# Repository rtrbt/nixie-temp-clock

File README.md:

# nixie-temp-clock
A modular nixie clock and thermometer based on [Exixe](https://github.com/dekuNukem/exixe).

## Features
- Shows temperature (in °C) and GPS-synchronized time
- Completely modular: the PCB only connects all modules via pin headers

## Hardware
To build your own you need:
- The PCB
- Ten Exixe modules
- One IN-19A, one IN-19V and eight IN-14 tubes
- A high-voltage power supply, as the nixies need 180V to glow. Has to be pin-compatible to [this one](https://www.ebay.com/itm/322511957768)
- A DS18B20 temperature sensor
- A GPS module which communicates via I²C, I recommend [this one](https://www.sparkfun.com/products/14414).
- An Arduino or compatible board in the MKR form factor, for example the Arduino MKR Zero

## Software
The Arduino sketch and required files can be found in the firmware folder. If you define USE_SERIAL, the Arduino will report errors raised during setup. Also it will report if the main loop took longer than 33ms, which would slow down the cross-fade effect.

## TODO
- Find some use for the tube back light (maybe temperature dependant?)
- Find some use for the MKR Zero's microSD slot
- Periodically display the current date (cross-fade)
- Build a case
- Add some buttons
- Maybe add another temperature sensor
- Port the board schematic from EAGLE to KiCad, also add a silk screen layer

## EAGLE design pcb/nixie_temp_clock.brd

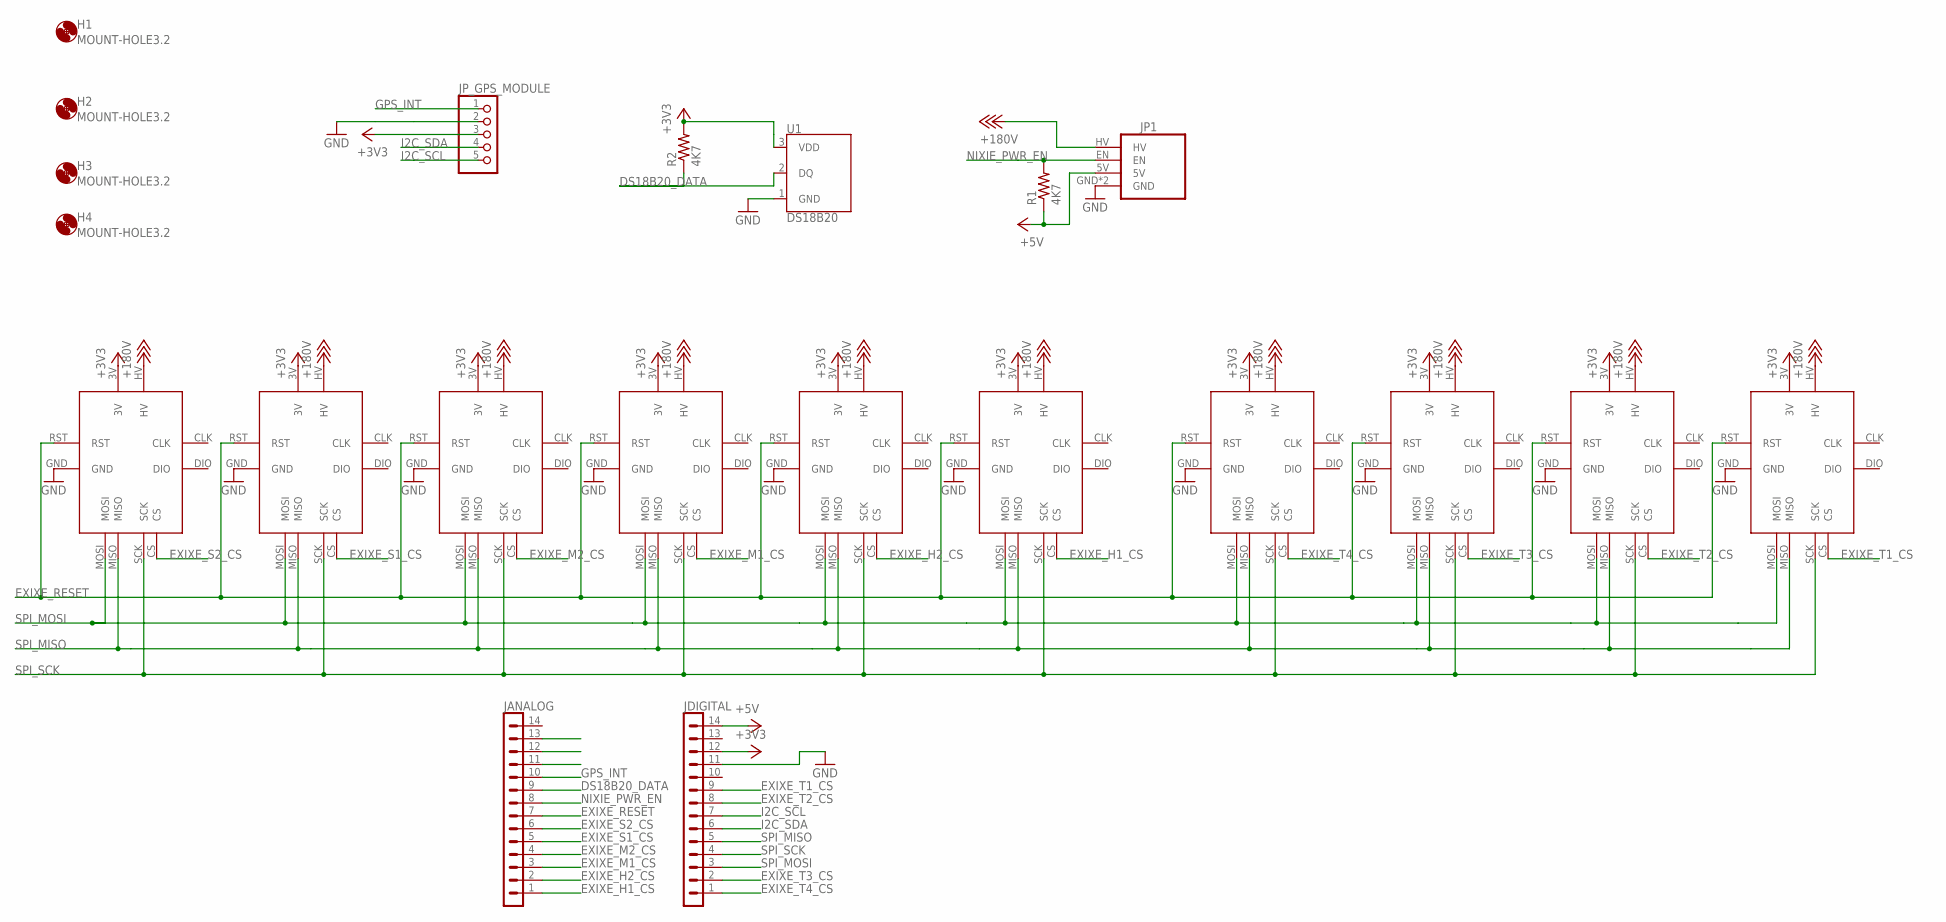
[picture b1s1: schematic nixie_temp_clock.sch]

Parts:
EXIXE_H1, EXIXE_H2: EXIXE_MODULE_EXIXE; EXIXE_MODULE_EXIXE_PAC
EXIXE_M1, EXIXE_M2: EXIXE_MODULE_EXIXE; EXIXE_MODULE_EXIXE_PAC
EXIXE_S1, EXIXE_S2: EXIXE_MODULE_EXIXE; EXIXE_MODULE_EXIXE_PAC
EXIXE_T1, EXIXE_T2, EXIXE_T3, EXIXE_T4: EXIXE_MODULE_EXIXE; EXIXE_MODULE_EXIXE_PAC
H1, H2, H3, H4: MOUNT-HOLE3.2; 3,2
JANALOG: ARDUINO-CONNECTORS_PINHD-1X14-SMTH; ARDUINO-CONNECTORS_1X14
JDIGITAL: ARDUINO-CONNECTORS_PINHD-1X14-SMTH; ARDUINO-CONNECTORS_1X14
JP1: EBAY_MODULETAOBAO; TAOBAO_PKG
JP_GPS_MODULE: PINHD-1X5; 1X05
R1, R2: 4K7; 0207/15
U1: DS18B20; TO-92-AMMO

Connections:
+3V3: EXIXE_H1.3V, EXIXE_H2.3V, EXIXE_M1.3V, EXIXE_M2.3V, EXIXE_S1.3V, EXIXE_S2.3V, EXIXE_T1.3V, EXIXE_T2.3V, EXIXE_T3.3V, EXIXE_T4.3V, JDIGITAL.12, JP_GPS_MODULE.3, R2.2, U1.3 (VDD)
+5V: JDIGITAL.14, JP1.5V, R1.1
+180V: EXIXE_H1.HV, EXIXE_H2.HV, EXIXE_M1.HV, EXIXE_M2.HV, EXIXE_S1.HV, EXIXE_S2.HV, EXIXE_T1.HV, EXIXE_T2.HV, EXIXE_T3.HV, EXIXE_T4.HV, JP1.HV
DS18B20_DATA: JANALOG.9, R2.1, U1.2 (DQ)
EXIXE_H1_CS: EXIXE_S2.CS, JANALOG.1
EXIXE_H2_CS: EXIXE_S1.CS, JANALOG.2
EXIXE_M1_CS: EXIXE_M2.CS, JANALOG.3
EXIXE_M2_CS: EXIXE_M1.CS, JANALOG.4
EXIXE_RESET: EXIXE_H1.RST, EXIXE_H2.RST, EXIXE_M1.RST, EXIXE_M2.RST, EXIXE_S1.RST, EXIXE_S2.RST, EXIXE_T1.RST, EXIXE_T2.RST, EXIXE_T3.RST, EXIXE_T4.RST, JANALOG.7
EXIXE_S1_CS: EXIXE_H2.CS, JANALOG.5
EXIXE_S2_CS: EXIXE_H1.CS, JANALOG.6
EXIXE_T1_CS: EXIXE_T4.CS, JDIGITAL.9
EXIXE_T2_CS: EXIXE_T3.CS, JDIGITAL.8
EXIXE_T3_CS: EXIXE_T2.CS, JDIGITAL.2
EXIXE_T4_CS: EXIXE_T1.CS, JDIGITAL.1
GND: EXIXE_H1.GND, EXIXE_H2.GND, EXIXE_M1.GND, EXIXE_M2.GND, EXIXE_S1.GND, EXIXE_S2.GND, EXIXE_T1.GND, EXIXE_T2.GND, EXIXE_T3.GND, EXIXE_T4.GND, JDIGITAL.11, JP1.GND, JP1.GND2 (GND), JP_GPS_MODULE.2, U1.1 (GND)
GPS_INT: JANALOG.10, JP_GPS_MODULE.1
I2C_SCL: JDIGITAL.7, JP_GPS_MODULE.5
I2C_SDA: JDIGITAL.6, JP_GPS_MODULE.4
NIXIE_PWR_EN: JANALOG.8, JP1.EN, R1.2
SPI_MISO: EXIXE_H1.MISO, EXIXE_H2.MISO, EXIXE_M1.MISO, EXIXE_M2.MISO, EXIXE_S1.MISO, EXIXE_S2.MISO, EXIXE_T1.MISO, EXIXE_T2.MISO, EXIXE_T3.MISO, EXIXE_T4.MISO, JDIGITAL.5
SPI_MOSI: EXIXE_H1.MOSI, EXIXE_H2.MOSI, EXIXE_M1.MOSI, EXIXE_M2.MOSI, EXIXE_S1.MOSI, EXIXE_S2.MOSI, EXIXE_T1.MOSI, EXIXE_T2.MOSI, EXIXE_T3.MOSI, EXIXE_T4.MOSI, JDIGITAL.3
SPI_SCK: EXIXE_H1.SCK, EXIXE_H2.SCK, EXIXE_M1.SCK, EXIXE_M2.SCK, EXIXE_S1.SCK, EXIXE_S2.SCK, EXIXE_T1.SCK, EXIXE_T2.SCK, EXIXE_T3.SCK, EXIXE_T4.SCK, JDIGITAL.4

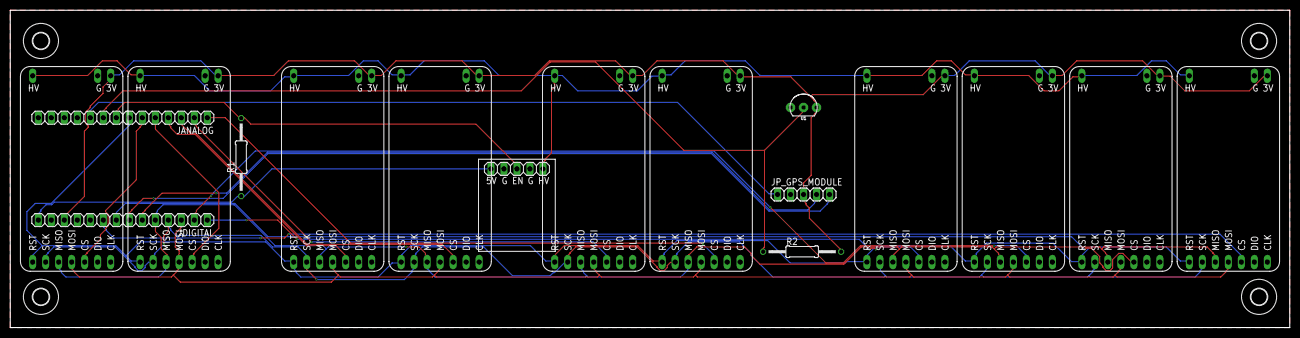
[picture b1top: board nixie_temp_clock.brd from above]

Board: 2 copper layers, 250.0 x 62.0 mm, 21 parts (0 on the bottom side), 23 nets.

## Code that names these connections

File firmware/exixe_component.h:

#pragma once

#include <Arduino.h>
#include <exixe.h>

const auto NIXIE_PWR_EN = A5;
const auto EXIXE_RESET = A6;

const auto EXIXE_H1_CS = 5;
const auto EXIXE_H2_CS = 4;
const auto EXIXE_M1_CS = 3;
const auto EXIXE_M2_CS = 2;
const auto EXIXE_S1_CS = 1;
const auto EXIXE_S2_CS = 0;
const auto EXIXE_T1_CS = 14;
const auto EXIXE_T2_CS = 13;
const auto EXIXE_T3_CS = 7;
const auto EXIXE_T4_CS = 6;

const decltype(EXIXE_H1_CS) exixe_cs_pins[10] = {
        EXIXE_H1_CS,
        EXIXE_H2_CS,
        EXIXE_M1_CS,
        EXIXE_M2_CS,
        EXIXE_S1_CS,
        EXIXE_S2_CS,
        EXIXE_T1_CS,
        EXIXE_T2_CS,
        EXIXE_T3_CS,
        EXIXE_T4_CS
};

const auto tube_count = sizeof(exixe_cs_pins) / sizeof(exixe_cs_pins[0]);

class exixe_component
{
public:
    bool setup();

    void report_setup_progress(float progress);

    void report_setup_error_and_exit();

    void loop(int hour, int minute, int second, float temperature);

private:
    void show_two_digits(int num, int tensNixieIdx, int onesNixieIdx);

    float temperature;
    exixe *nixies;
};

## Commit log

2018-08-13 Added arduino firmware.
2018-08-13 Added board schematic.
2018-08-14 Added image of the complete clock.

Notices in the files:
parts and their libraries:
SparkFun-Sensors: Licensing: Creative Commons ShareAlike 4.0 International - https://creativecommons.org/licenses/by-sa/4.0
